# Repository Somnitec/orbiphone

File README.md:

Orbiphone (formerly WAMBAM or Toonpad)

A musical instrument making tones based on capacitive sensors.

todo:
Improve calibration algorhythmn
Make all buttons same color
Make button color related to tones pressed
Add subtle dynamic effects (bitcrushed reverb? multiply? things when buttons keep pressed?)

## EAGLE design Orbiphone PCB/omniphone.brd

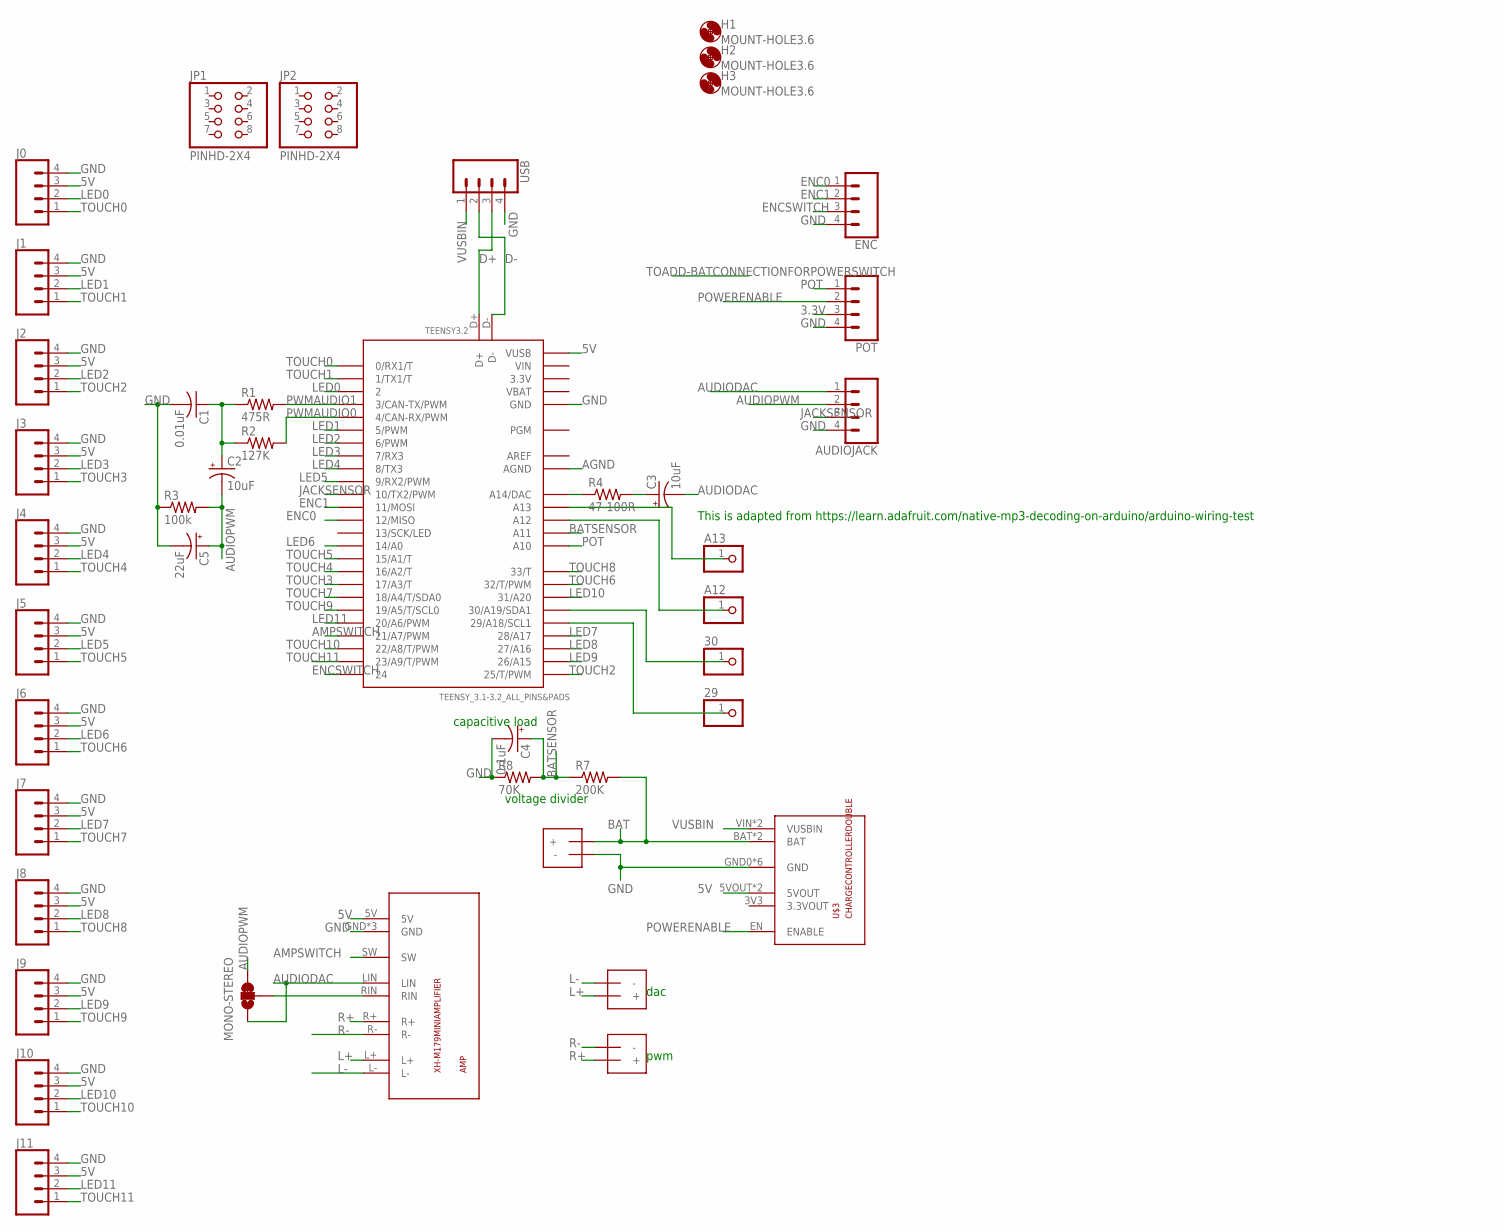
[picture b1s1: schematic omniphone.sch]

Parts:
29, 30: PINHD-1X1; 1X01
A12, A13: PINHD-1X1; 1X01
AMP: XH-M179MINIAMPLIFIER; XH-M179AMP
AUDIOJACK: CONN_04POLAR_LOCK; MOLEX-1X4_LOCK
BATTERY: SPEAKERTERMINAL-3.5MM; 1X2-3.5MM
C1: 0.01uF; C025-024X044
C2, C3: 10uF; E2-4
C4: 0.1uF; E2-4
C5: 22uF; E2-4
ENC: CONN_04POLAR_LOCK; MOLEX-1X4_LOCK
H1, H2, H3: MOUNT-HOLE3.6; 3,6
J0, J1, J2, J3, J4, J5, J6, J7, J8, J9, J10, J11: CONN_04POLAR_LOCK; MOLEX-1X4_LOCK
JP1, JP2: PINHD-2X4; 2X04
MONO-STEREO: JUMPER-SMT_3_1-NC_TRACE_SILK; SMT-JUMPER_3_1-NC_TRACE_SILK
POT: CONN_04POLAR_LOCK; MOLEX-1X4_LOCK
R1: 475R; 0204V
R2: 127K; 0204V
R3: 100k; 0204V
R4: 47-100R; 0204V
R7: 200K; 0204V
R8: 70K; 0204V
SPEAKERDAC: SPEAKERTERMINAL-3.5MM; 1X2-3.5MM
SPEAKERPWM: SPEAKERTERMINAL-3.5MM; 1X2-3.5MM
TEENSY3.2: TEENSY_3.1-3.2_ALL_PINS&PADS; TEENSY_3.0-3.2_ALL_PINS_&_PADS
U$3: CHARGECONTROLLERDOUBLE
USB: CONN_04POLAR_LOCK; MOLEX-1X4_LOCK

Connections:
3.3V: POT.3, TEENSY3.2.3.3V, TEENSY3.2.3.3V1 (3.3V), TEENSY3.2.3.3V2 (3.3V)
5V: AMP.5V, J0.3, J1.3, J2.3, J3.3, J4.3, J5.3, J6.3, J7.3, J8.3, J9.3, J10.3, J11.3, TEENSY3.2.VUSB, TEENSY3.2.VUSB1 (VUSB), U$3.5VOUT, U$3.5VOUT1 (5VOUT)
AGND: TEENSY3.2.AGND
AMPSWITCH: AMP.SW, TEENSY3.2.21/A7 (21/A7/PWM)
AREF: TEENSY3.2.AREF
AUDIODAC: AMP.LIN, AUDIOJACK.1, C3.-, MONO-STEREO.1
AUDIOPWM: AUDIOJACK.2, C2.-, C5.+, MONO-STEREO.3, R3.2
BAT: BATTERY.+, R7.2, U$3.BAT, U$3.BAT1 (BAT)
BATSENSOR: C4.+, R7.1, R8.2, TEENSY3.2.A11
D+: TEENSY3.2.D+, USB.3
D-: TEENSY3.2.D-, USB.2
ENC0: ENC.1, TEENSY3.2.12 (12/MISO)
ENC1: ENC.2, TEENSY3.2.11 (11/MOSI)
ENCSWITCH: ENC.3, TEENSY3.2.24
GND: AMP.GND, AMP.GND1 (GND), AMP.GND2 (GND), AUDIOJACK.4, BATTERY.-, C1.2, C4.-, C5.-, ENC.4, J0.4, J1.4, J2.4, J3.4, J4.4, J5.4, J6.4, J7.4, J8.4, J9.4, J10.4, J11.4, POT.4, R3.1, R8.1, TEENSY3.2.GND, TEENSY3.2.GND1 (GND), TEENSY3.2.GND2 (GND), TEENSY3.2.GND3 (GND), U$3.GND0 (GND), U$3.GND1 (GND), U$3.GND2 (GND), U$3.GND3 (GND), U$3.GND4 (GND), U$3.GND5 (GND), USB.4
JACKSENSOR: AUDIOJACK.3, TEENSY3.2.10 (10/TX2/PWM)
L+: AMP.L+, SPEAKERDAC.+
L-: AMP.L-, SPEAKERDAC.-
LED0: J0.2, TEENSY3.2.2
LED1: J1.2, TEENSY3.2.5 (5/PWM)
LED2: J2.2, TEENSY3.2.6 (6/PWM)
LED3: J3.2, TEENSY3.2.7 (7/RX3)
LED4: J4.2, TEENSY3.2.8 (8/TX3)
LED5: J5.2, TEENSY3.2.9 (9/RX2/PWM)
LED6: J6.2, TEENSY3.2.14/A0
LED7: J7.2, TEENSY3.2.28 (28/A17)
LED8: J8.2, TEENSY3.2.27 (27/A16)
LED9: J9.2, TEENSY3.2.26 (26/A15)
LED10: J10.2, TEENSY3.2.31 (31/A20)
LED11: J11.2, TEENSY3.2.20/A6 (20/A6/PWM)
unnamed: C1.1, C2.+, R1.1, R2.1
unnamed: A13.1, TEENSY3.2.A13
unnamed: A12.1, TEENSY3.2.A12
unnamed: R4.1, TEENSY3.2.RESET/DAC (A14/DAC)
unnamed: 30.1, TEENSY3.2.30 (30/A19/SDA1)
unnamed: C3.+, R4.2
unnamed: 29.1, TEENSY3.2.29 (29/A18/SCL1)
POT: POT.1, TEENSY3.2.A10
POWERENABLE: POT.2, U$3.EN (ENABLE)
PWMAUDIO0: R2.2, TEENSY3.2.4 (4/CAN-RX/PWM)
PWMAUDIO1: R1.2, TEENSY3.2.3 (3/CAN-TX/PWM)
R+: AMP.R+, SPEAKERPWM.+
R-: AMP.R-, SPEAKERPWM.-
RIN: AMP.RIN, MONO-STEREO.2
TOUCH0: J0.1, TEENSY3.2.0 (0/RX1/T)
TOUCH1: J1.1, TEENSY3.2.1 (1/TX1/T)
TOUCH2: J2.1, TEENSY3.2.25 (25/T/PWM)
TOUCH3: J3.1, TEENSY3.2.17/A3 (17/A3/T)
TOUCH4: J4.1, TEENSY3.2.16/A2 (16/A2/T)
TOUCH5: J5.1, TEENSY3.2.15/A1 (15/A1/T)
TOUCH6: J6.1, TEENSY3.2.32 (32/T/PWM)
TOUCH7: J7.1, TEENSY3.2.18/A4 (18/A4/T/SDA0)
TOUCH8: J8.1, TEENSY3.2.33 (33/T)
TOUCH9: J9.1, TEENSY3.2.19/A5 (19/A5/T/SCL0)
TOUCH10: J10.1, TEENSY3.2.22/A8 (22/A8/T/PWM)
TOUCH11: J11.1, TEENSY3.2.23/A9 (23/A9/T/PWM)
VBAT: TEENSY3.2.VBAT
VIN: TEENSY3.2.VIN
VUSBIN: U$3.VIN (VUSBIN), U$3.VIN1 (VUSBIN), USB.1

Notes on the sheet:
This is adapted from https://learn.adafruit.com/native-mp3-decoding-on-arduino/arduino-wiring-test
dac
pwm
voltage divider
capacitive load

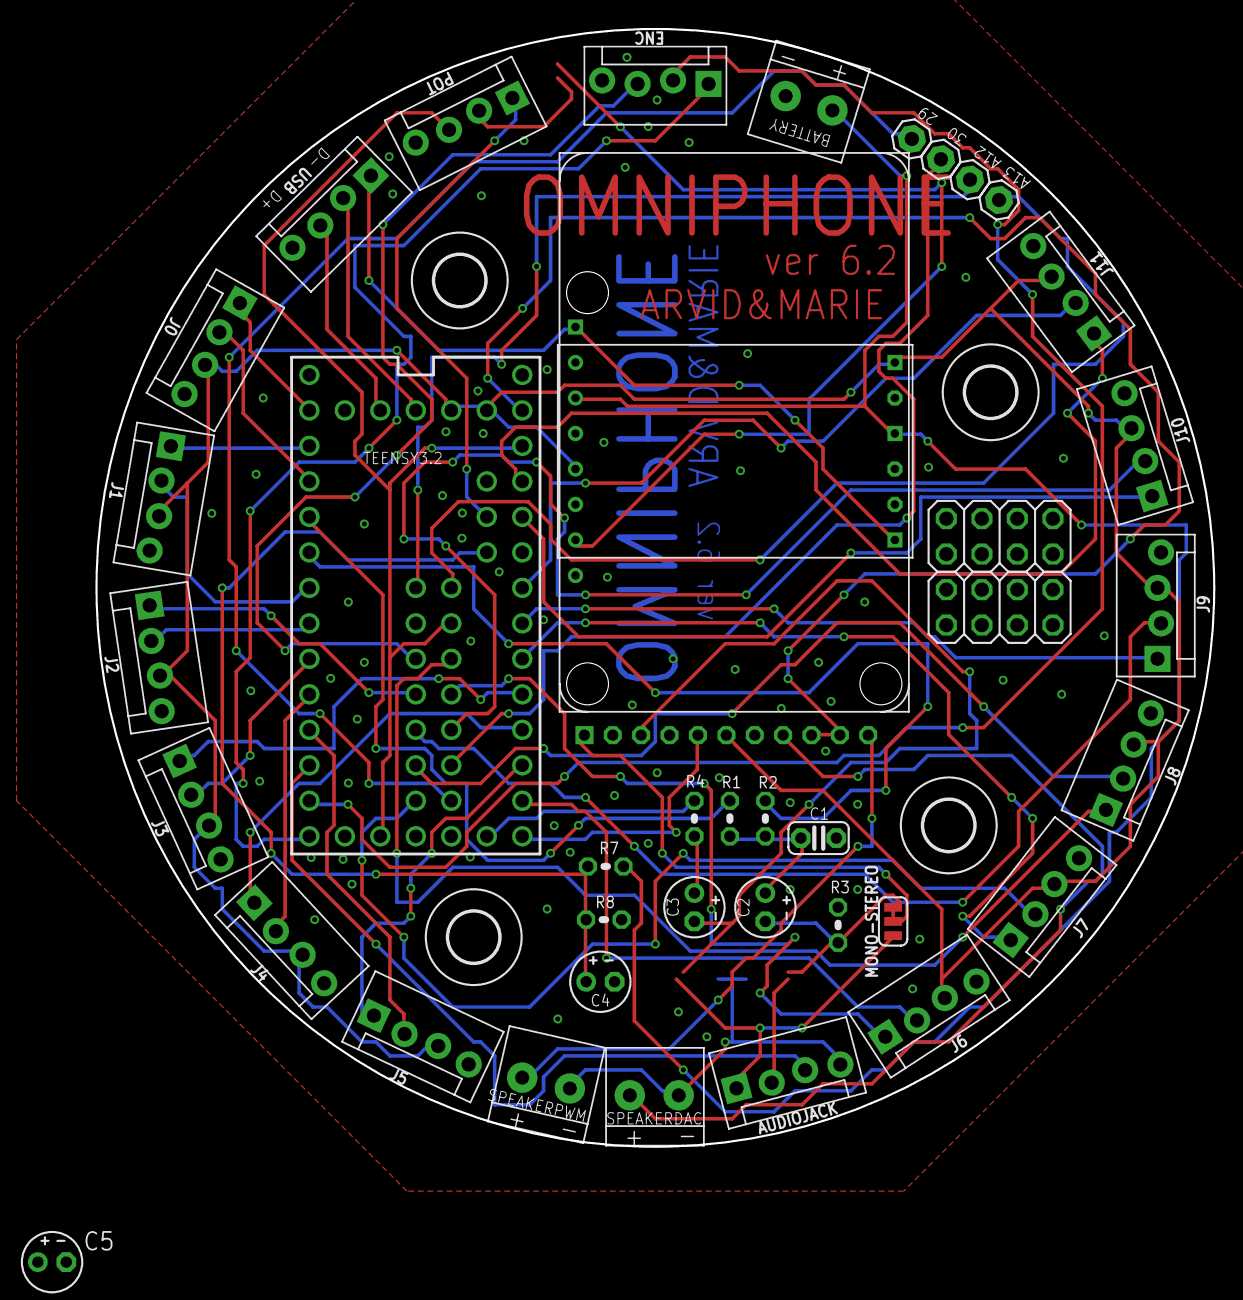
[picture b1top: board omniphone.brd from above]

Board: 2 copper layers, 80.0 x 80.0 mm, 44 parts (1 on the bottom side), 55 nets.

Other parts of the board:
H4: MOUNT-HOLE3.6; 3,6

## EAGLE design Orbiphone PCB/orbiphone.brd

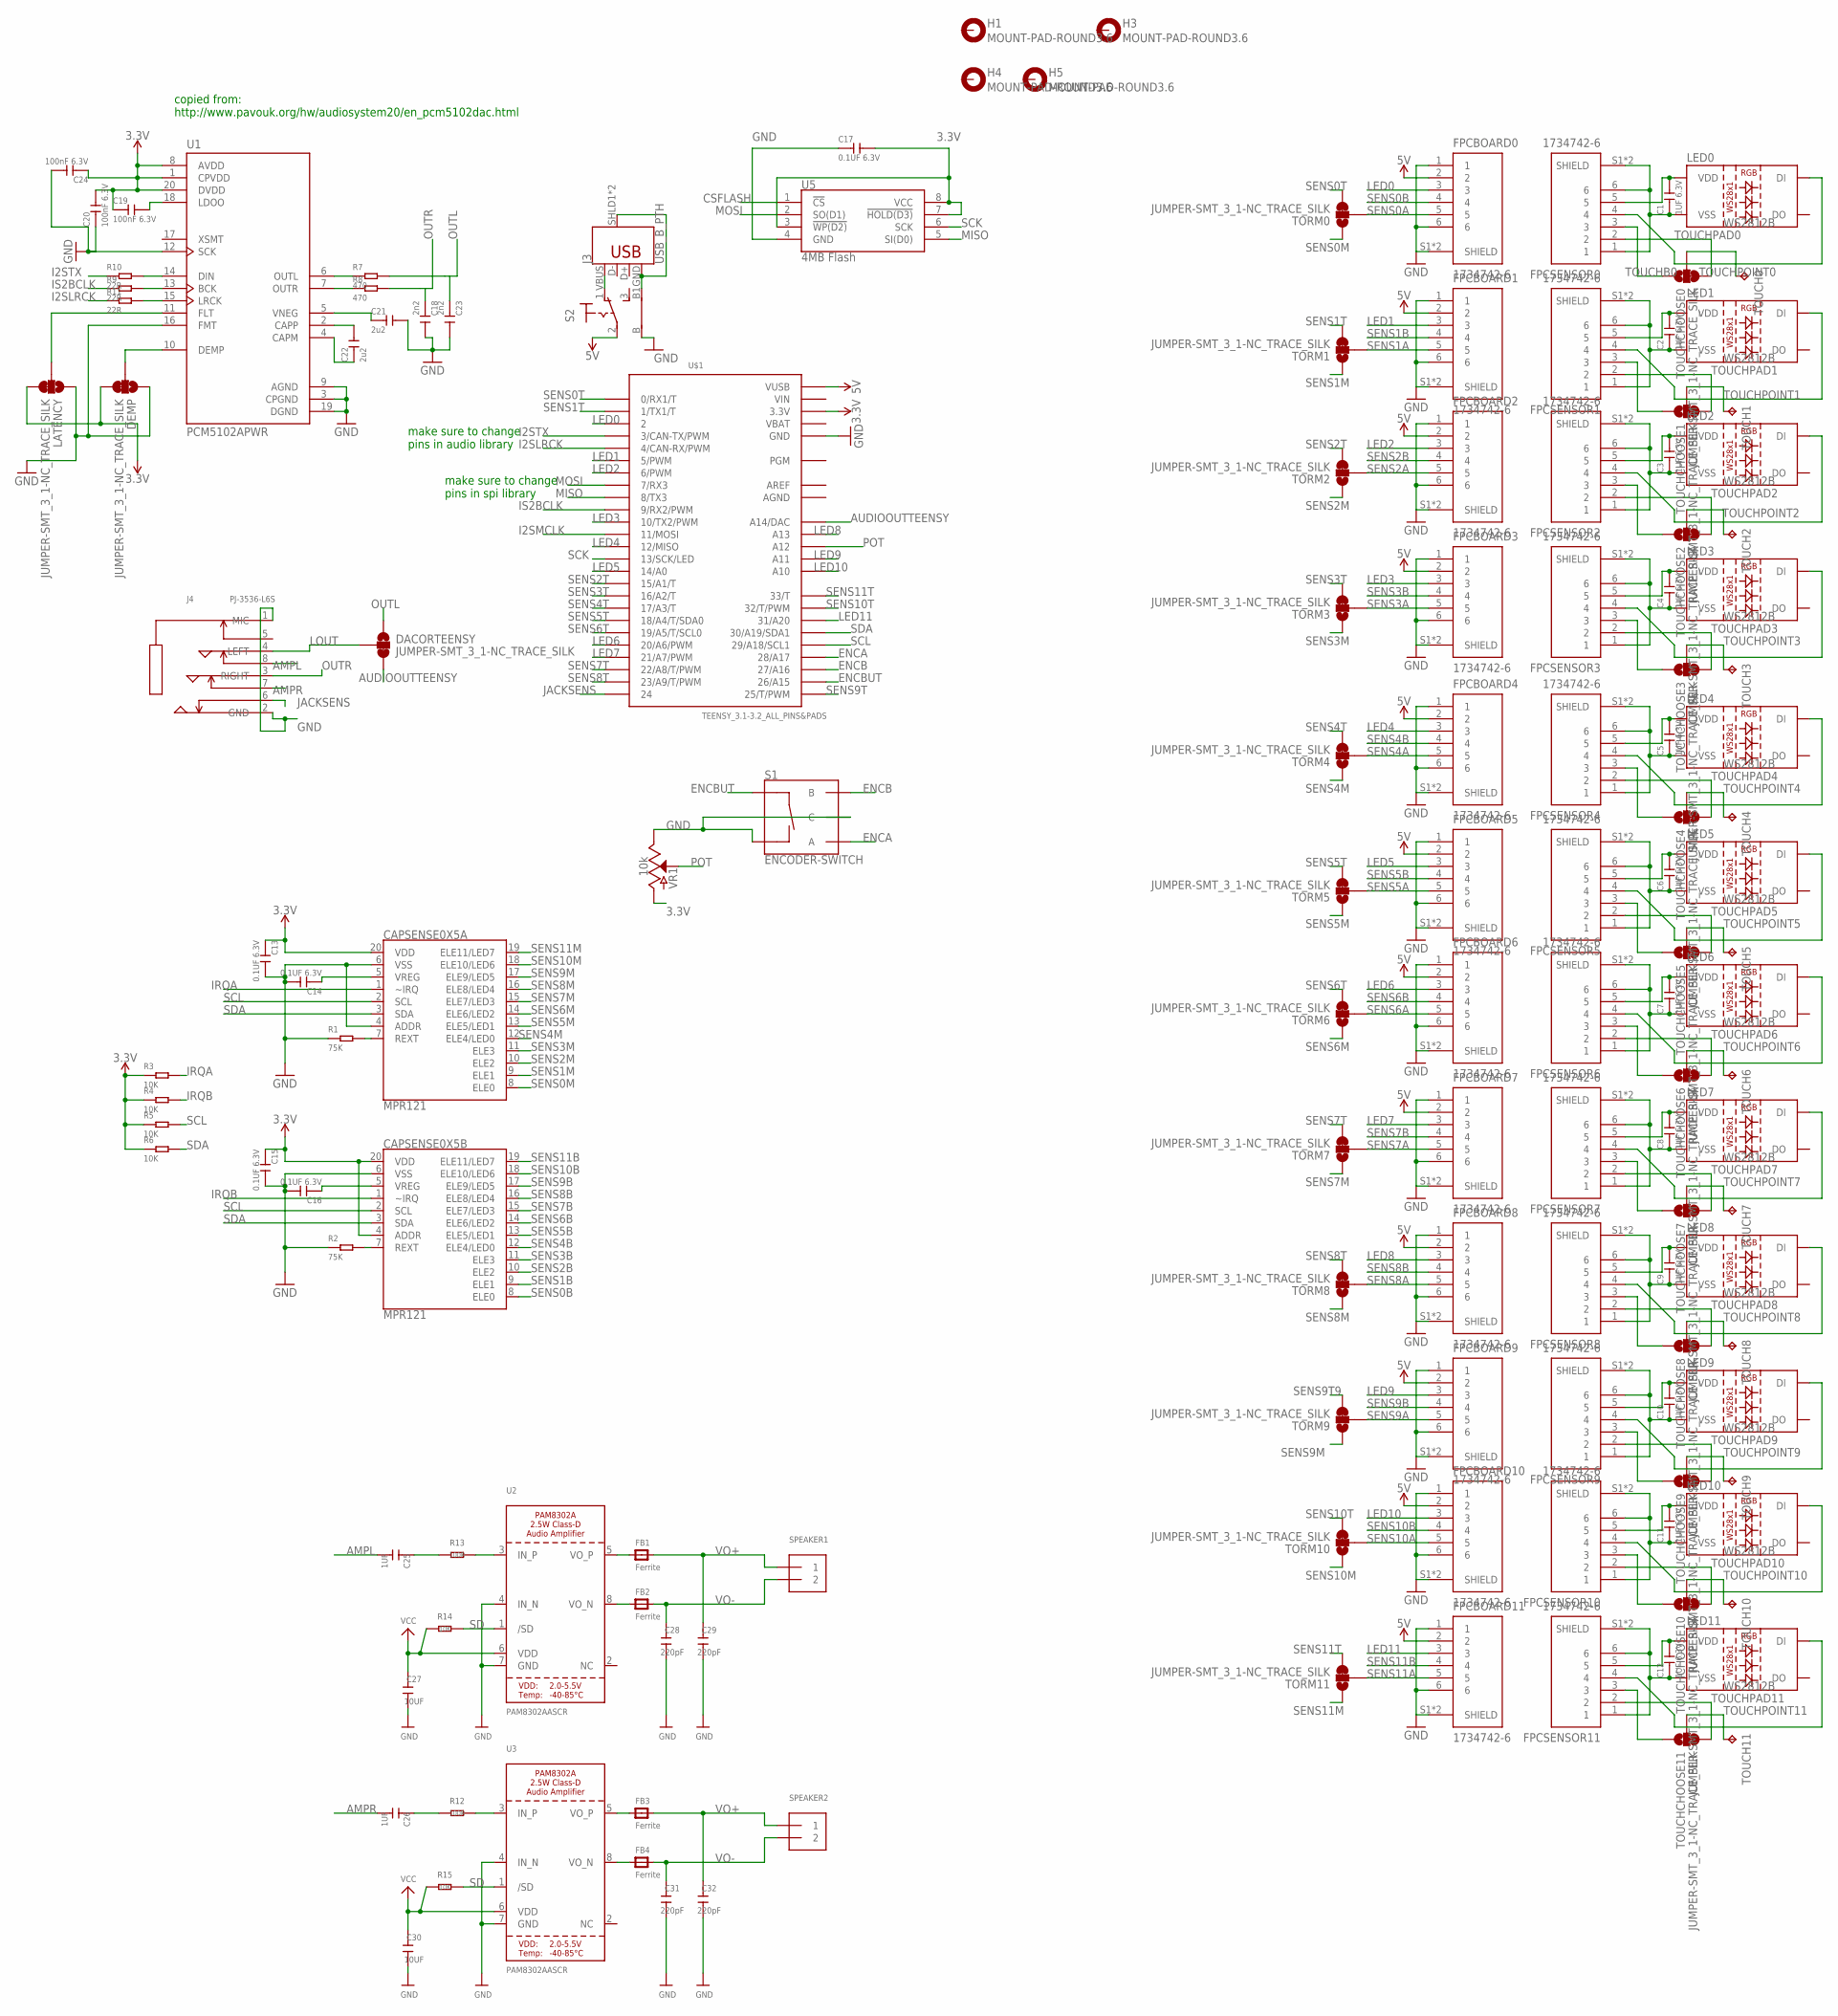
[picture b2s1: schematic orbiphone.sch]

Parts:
C1, C2, C3, C4, C5, C6, C7, C8, C9, C10, C11, C12: 1UF 6.3V; C0402
C13, C14, C15, C16, C17: 0.1UF 6.3V; C0402
C18, C23: 2n2; C0402
C19, C20, C24: 100nF 6.3V; C0402
C21, C22: 2u2; C0402
C25, C26: 1UF; C0402
C27, C30: 10UF; C0402
C28, C29, C31, C32: 220pF; C0402
CAPSENSE0X5A, CAPSENSE0X5B: MPR121; QFN-20
DACORTEENSY: JUMPER-SMT_3_1-NC_TRACE_SILK; SMT-JUMPER_3_1-NC_TRACE_SILK
DEMP: JUMPER-SMT_3_1-NC_TRACE_SILK; SMT-JUMPER_3_1-NC_TRACE_SILK
FB1, FB2, FB3, FB4: Ferrite; _0805
FPCBOARD0, FPCBOARD1, FPCBOARD2, FPCBOARD3, FPCBOARD4, FPCBOARD5, FPCBOARD6, FPCBOARD7, FPCBOARD8, FPCBOARD9, FPCBOARD10, FPCBOARD11: 1734742-6; TE_1734742-6
FPCSENSOR0, FPCSENSOR1, FPCSENSOR2, FPCSENSOR3, FPCSENSOR4, FPCSENSOR5, FPCSENSOR6, FPCSENSOR7, FPCSENSOR8, FPCSENSOR9, FPCSENSOR10, FPCSENSOR11: 1734742-6; TE_1734742-6
H1, H3, H4, H5: MOUNT-PAD-ROUND3.6; 3,6-PAD
J3: USB_B_PTH; USB-B-PTH
J4: PJ-3536-L6S; AUDIO8P-SMD-3.5-14.5X6X5MM
LATENCY: JUMPER-SMT_3_1-NC_TRACE_SILK; SMT-JUMPER_3_1-NC_TRACE_SILK
LED0, LED1, LED2, LED3, LED4, LED5, LED6, LED7, LED8, LED9, LED10, LED11: WS2812B
R1, R2: 75K; R0603
R3, R4, R5, R6: 10K; R0603
R7, R8: 470; R0603
R9, R10, R11: 22R; R0603
R12, R13: 100R; R0805
R14, R15: 10K; R0805
S1: ENCODER-SWITCH; ROTARY_ENC_PLAIN
S2: 316-917
SPEAKER1, SPEAKER2: TERMBLOCK_1X2; TERMBLOCK_1X2-3.5MM
TORM0, TORM1, TORM2, TORM3, TORM4, TORM5, TORM6, TORM7, TORM8, TORM9, TORM10, TORM11: JUMPER-SMT_3_1-NC_TRACE_SILK; SMT-JUMPER_3_1-NC_TRACE_SILK
TOUCH0, TOUCH1, TOUCH2, TOUCH3, TOUCH4, TOUCH5, TOUCH6, TOUCH7, TOUCH8, TOUCH9, TOUCH10, TOUCH11: TPPAD1-13; P1-13
TOUCHCHOOSE0, TOUCHCHOOSE1, TOUCHCHOOSE2, TOUCHCHOOSE3, TOUCHCHOOSE4, TOUCHCHOOSE5, TOUCHCHOOSE6, TOUCHCHOOSE7, TOUCHCHOOSE8, TOUCHCHOOSE9, TOUCHCHOOSE10, TOUCHCHOOSE11: JUMPER-SMT_3_1-NC_TRACE_SILK; SMT-JUMPER_3_1-NC_TRACE_SILK
U1: PCM5102APWR; SOP65P640X120-20N
U2, U3: PAM8302AASCR; MSOP8_0.65MM
U5: 4MB Flash; SO08
U$1: TEENSY_3.1-3.2_ALL_PINS&PADS; TEENSY_3.0-3.2_ALL_PINS_&_PADS
VR1: 10k; POT-PTH-ALPS-KIT

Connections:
3.3V: C13.1, C15.1, C17.2, C19.1, C20.2, C24.1, CAPSENSE0X5A.20 (VDD), CAPSENSE0X5B.4 (ADDR), CAPSENSE0X5B.20 (VDD), DEMP.3, LATENCY.3, R3.1, R4.1, R5.1, R6.1, U1.1 (CPVDD), U1.8 (AVDD), U1.20 (DVDD), U5.3 (!WP(D2)), U5.7 (!HOLD(D3)), U5.8 (VCC), U$1.3.3V, U$1.3.3V1 (3.3V), U$1.3.3V2 (3.3V), VR1.P$3 (A)
5V: FPCBOARD0.2, FPCBOARD1.2, FPCBOARD2.2, FPCBOARD3.2, FPCBOARD4.2, FPCBOARD5.2, FPCBOARD6.2, FPCBOARD7.2, FPCBOARD8.2, FPCBOARD9.2, FPCBOARD10.2, FPCBOARD11.2, S2.2, U$1.VUSB
AGND: U$1.AGND
AMPL: C25.2, J4.8
AMPR: C26.2, J4.7
AREF: U$1.AREF
AUDIOOUTTEENSY: DACORTEENSY.3, U$1.RESET/DAC (A14/DAC)
CSFLASH: U5.1 (!CS)
ENCA: S1.A, U$1.28 (28/A17)
ENCB: S1.B, U$1.27 (27/A16)
ENCBUT: S1.SW+, U$1.26 (26/A15)
GND: C13.2, C14.2, C15.2, C16.2, C17.1, C18.2, C20.1, C21.2, C23.2, C24.2, C27.2, C28.2, C29.2, C30.2, C31.2, C32.2, CAPSENSE0X5A.4 (ADDR), CAPSENSE0X5A.6 (VSS), CAPSENSE0X5B.6 (VSS), DEMP.1, FPCBOARD0.1, FPCBOARD0.6, FPCBOARD0.S1 (SHIELD), FPCBOARD0.S2 (SHIELD), FPCBOARD1.1, FPCBOARD1.6, FPCBOARD1.S1 (SHIELD), FPCBOARD1.S2 (SHIELD), FPCBOARD2.1, FPCBOARD2.6, FPCBOARD2.S1 (SHIELD), FPCBOARD2.S2 (SHIELD), FPCBOARD3.1, FPCBOARD3.6, FPCBOARD3.S1 (SHIELD), FPCBOARD3.S2 (SHIELD), FPCBOARD4.1, FPCBOARD4.6, FPCBOARD4.S1 (SHIELD), FPCBOARD4.S2 (SHIELD), FPCBOARD5.1, FPCBOARD5.6, FPCBOARD5.S1 (SHIELD), FPCBOARD5.S2 (SHIELD), FPCBOARD6.1, FPCBOARD6.6, FPCBOARD6.S1 (SHIELD), FPCBOARD6.S2 (SHIELD), FPCBOARD7.1, FPCBOARD7.6, FPCBOARD7.S1 (SHIELD), FPCBOARD7.S2 (SHIELD), FPCBOARD8.1, FPCBOARD8.6, FPCBOARD8.S1 (SHIELD), FPCBOARD8.S2 (SHIELD), FPCBOARD9.1, FPCBOARD9.6, FPCBOARD9.S1 (SHIELD), FPCBOARD9.S2 (SHIELD), FPCBOARD10.1, FPCBOARD10.6, FPCBOARD10.S1 (SHIELD), FPCBOARD10.S2 (SHIELD), FPCBOARD11.1, FPCBOARD11.6, FPCBOARD11.S1 (SHIELD), FPCBOARD11.S2 (SHIELD), J4.1 (MIC), J4.2 (GND), LATENCY.1, R1.1, R2.1, S1.C, S1.SW-, S2.B, U1.3 (CPGND), U1.9 (AGND), U1.12 (SCK), U1.16 (FMT), U1.19 (DGND), U2.4 (IN_N), U2.7 (GND), U3.4 (IN_N), U3.7 (GND), U5.4 (GND), U$1.GND, U$1.GND1 (GND), U$1.GND2 (GND), VR1.P$1 (E)
I2SLRCK: R11.1, U$1.4 (4/CAN-RX/PWM)
I2SMCLK: U$1.11 (11/MOSI)
I2STX: R10.1, U$1.3 (3/CAN-TX/PWM)
IRQA: CAPSENSE0X5A.1 (~IRQ), R3.2
IRQB: CAPSENSE0X5B.1 (~IRQ), R4.2
IS2BCLK: R9.1, U$1.9 (9/RX2/PWM)
JACKSENS: J4.6, U$1.24
LED0: FPCBOARD0.3, U$1.2
LED1: FPCBOARD1.3, U$1.5 (5/PWM)
LED2: FPCBOARD2.3, U$1.6 (6/PWM)
LED3: FPCBOARD3.3, U$1.10 (10/TX2/PWM)
LED4: FPCBOARD4.3, U$1.12 (12/MISO)
LED5: FPCBOARD5.3, U$1.14/A0
LED6: FPCBOARD6.3, U$1.20/A6 (20/A6/PWM)
LED7: FPCBOARD7.3, U$1.21/A7 (21/A7/PWM)
LED8: FPCBOARD8.3, U$1.A13
LED9: FPCBOARD9.3, U$1.A11
LED10: FPCBOARD10.3, U$1.A10
LED11: FPCBOARD11.3, U$1.31 (31/A20)
LOUT: DACORTEENSY.2, J4.4 (LEFT)
MISO: U5.5 (SI(D0)), U$1.8 (8/TX3)
MOSI: U5.2 (SO(D1)), U$1.7 (7/RX3)
unnamed: C1.1, FPCSENSOR0.1, FPCSENSOR0.6, FPCSENSOR0.S1 (SHIELD), FPCSENSOR0.S2 (SHIELD), LED0.3 (VSS)
unnamed: C2.1, FPCSENSOR1.1, FPCSENSOR1.6, FPCSENSOR1.S1 (SHIELD), FPCSENSOR1.S2 (SHIELD), LED1.3 (VSS)
unnamed: C1.2, FPCSENSOR0.5, LED0.1 (VDD)
unnamed: FPCSENSOR0.4, LED0.4 (DI)
unnamed: C2.2, FPCSENSOR1.5, LED1.1 (VDD)
unnamed: FPCSENSOR1.4, LED1.4 (DI)
unnamed: FPCSENSOR1.3, TOUCHCHOOSE1.1
unnamed: C3.1, FPCSENSOR2.1, FPCSENSOR2.6, FPCSENSOR2.S1 (SHIELD), FPCSENSOR2.S2 (SHIELD), LED2.3 (VSS)
unnamed: C3.2, FPCSENSOR2.5, LED2.1 (VDD)
unnamed: FPCSENSOR2.4, LED2.4 (DI)
unnamed: FPCSENSOR2.3, TOUCHCHOOSE2.1
unnamed: C4.1, FPCSENSOR3.1, FPCSENSOR3.6, FPCSENSOR3.S1 (SHIELD), FPCSENSOR3.S2 (SHIELD), LED3.3 (VSS)
unnamed: C4.2, FPCSENSOR3.5, LED3.1 (VDD)
unnamed: FPCSENSOR3.4, LED3.4 (DI)
unnamed: FPCSENSOR3.3, TOUCHCHOOSE3.1
unnamed: C5.1, FPCSENSOR4.1, FPCSENSOR4.6, FPCSENSOR4.S1 (SHIELD), FPCSENSOR4.S2 (SHIELD), LED4.3 (VSS)
unnamed: C5.2, FPCSENSOR4.5, LED4.1 (VDD)
unnamed: FPCSENSOR4.4, LED4.4 (DI)
unnamed: FPCSENSOR4.3, TOUCHCHOOSE4.1
unnamed: C6.1, FPCSENSOR5.1, FPCSENSOR5.6, FPCSENSOR5.S1 (SHIELD), FPCSENSOR5.S2 (SHIELD), LED5.3 (VSS)
unnamed: C6.2, FPCSENSOR5.5, LED5.1 (VDD)
unnamed: FPCSENSOR5.4, LED5.4 (DI)
unnamed: FPCSENSOR5.3, TOUCHCHOOSE5.1
unnamed: C7.1, FPCSENSOR6.1, FPCSENSOR6.6, FPCSENSOR6.S1 (SHIELD), FPCSENSOR6.S2 (SHIELD), LED6.3 (VSS)
unnamed: C7.2, FPCSENSOR6.5, LED6.1 (VDD)
unnamed: FPCSENSOR6.4, LED6.4 (DI)
unnamed: C14.1, CAPSENSE0X5A.5 (VREG)
unnamed: CAPSENSE0X5A.7 (REXT), R1.2
unnamed: J3.GND, J3.SHLD1 (SHIELD), J3.SHLD2 (SHIELD), S2.B1
unnamed: J3.VBUS, S2.1 (O)
unnamed: C16.1, CAPSENSE0X5B.5 (VREG)
unnamed: CAPSENSE0X5B.7 (REXT), R2.2
unnamed: R10.2, U1.14 (DIN)
unnamed: R9.2, U1.13 (BCK)
unnamed: R11.2, U1.15 (LRCK)
unnamed: C19.2, U1.18 (LDOO)
unnamed: C22.2, U1.2 (CAPP)
unnamed: C22.1, U1.4 (CAPM)
unnamed: C21.1, U1.5 (VNEG)
unnamed: R7.1, U1.6 (OUTL)
unnamed: R8.1, U1.7 (OUTR)
unnamed: LATENCY.2, U1.11 (FLT)
unnamed: DEMP.2, U1.10 (DEMP)
unnamed: R12.2, U3.3 (IN_P)
unnamed: R13.2, U2.3 (IN_P)
unnamed: FB4.1, U3.8 (VO_N)
unnamed: FB2.1, U2.8 (VO_N)
unnamed: FB1.1, U2.5 (VO_P)
unnamed: C25.1, R13.1
unnamed: FB3.1, U3.5 (VO_P)
unnamed: C26.1, R12.1
unnamed: FPCSENSOR6.3, TOUCHCHOOSE6.1
unnamed: C8.1, FPCSENSOR7.1, FPCSENSOR7.6, FPCSENSOR7.S1 (SHIELD), FPCSENSOR7.S2 (SHIELD), LED7.3 (VSS)
unnamed: C8.2, FPCSENSOR7.5, LED7.1 (VDD)
unnamed: FPCSENSOR7.4, LED7.4 (DI)
unnamed: FPCSENSOR7.3, TOUCHCHOOSE7.1
unnamed: C9.1, FPCSENSOR8.1, FPCSENSOR8.6, FPCSENSOR8.S1 (SHIELD), FPCSENSOR8.S2 (SHIELD), LED8.3 (VSS)
unnamed: C9.2, FPCSENSOR8.5, LED8.1 (VDD)
unnamed: FPCSENSOR8.4, LED8.4 (DI)
unnamed: FPCSENSOR8.3, TOUCHCHOOSE8.1
unnamed: C10.1, FPCSENSOR9.1, FPCSENSOR9.6, FPCSENSOR9.S1 (SHIELD), FPCSENSOR9.S2 (SHIELD), LED9.3 (VSS)
unnamed: C10.2, FPCSENSOR9.5, LED9.1 (VDD)
unnamed: FPCSENSOR9.4, LED9.4 (DI)
unnamed: FPCSENSOR9.3, TOUCHCHOOSE9.1
unnamed: C11.1, FPCSENSOR10.1, FPCSENSOR10.6, FPCSENSOR10.S1 (SHIELD), FPCSENSOR10.S2 (SHIELD), LED10.3 (VSS)
unnamed: C11.2, FPCSENSOR10.5, LED10.1 (VDD)
unnamed: FPCSENSOR10.4, LED10.4 (DI)
unnamed: FPCSENSOR10.3, TOUCHCHOOSE10.1
unnamed: C12.1, FPCSENSOR11.1, FPCSENSOR11.6, FPCSENSOR11.S1 (SHIELD), FPCSENSOR11.S2 (SHIELD), LED11.3 (VSS)
unnamed: C12.2, FPCSENSOR11.5, LED11.1 (VDD)
unnamed: FPCSENSOR11.4, LED11.4 (DI)
unnamed: FPCSENSOR11.3, TOUCHCHOOSE11.1
OUTL: C23.1, DACORTEENSY.1, R7.2
OUTR: C18.1, J4.3 (RIGHT), R8.2
POT: U$1.A12, VR1.P$2 (S)
SCK: U5.6 (SCK), U$1.13 (13/SCK/LED)
SCL: CAPSENSE0X5A.2 (SCL), CAPSENSE0X5B.2 (SCL), R5.2, U$1.29 (29/A18/SCL1)
SD: R14.2, R15.2, U2.1 (/SD), U3.1 (/SD)
SDA: CAPSENSE0X5A.3 (SDA), CAPSENSE0X5B.3 (SDA), R6.2, U$1.30 (30/A19/SDA1)
SENS0A: FPCBOARD0.5, TORM0.2
SENS0B: CAPSENSE0X5B.8 (ELE0), FPCBOARD0.4
SENS0M: CAPSENSE0X5A.8 (ELE0), TORM0.1
SENS0T: TORM0.3, U$1.0 (0/RX1/T)
SENS1A: FPCBOARD1.5, TORM1.2
SENS1B: CAPSENSE0X5B.9 (ELE1), FPCBOARD1.4
SENS1M: CAPSENSE0X5A.9 (ELE1), TORM1.1
SENS1T: TORM1.3, U$1.1 (1/TX1/T)
SENS2A: FPCBOARD2.5, TORM2.2
SENS2B: CAPSENSE0X5B.10 (ELE2), FPCBOARD2.4
SENS2M: CAPSENSE0X5A.10 (ELE2), TORM2.1
SENS2T: TORM2.3, U$1.15/A1 (15/A1/T)
SENS3A: FPCBOARD3.5, TORM3.2
SENS3B: CAPSENSE0X5B.11 (ELE3), FPCBOARD3.4
SENS3M: CAPSENSE0X5A.11 (ELE3), TORM3.1
SENS3T: TORM3.3, U$1.16/A2 (16/A2/T)
SENS4A: FPCBOARD4.5, TORM4.2
SENS4B: CAPSENSE0X5B.12 (ELE4/LED0), FPCBOARD4.4
SENS4M: CAPSENSE0X5A.12 (ELE4/LED0), TORM4.1
SENS4T: TORM4.3, U$1.17/A3 (17/A3/T)
SENS5A: FPCBOARD5.5, TORM5.2
SENS5B: CAPSENSE0X5B.13 (ELE5/LED1), FPCBOARD5.4
SENS5M: CAPSENSE0X5A.13 (ELE5/LED1), TORM5.1
SENS5T: TORM5.3, U$1.18/A4 (18/A4/T/SDA0)
SENS6A: FPCBOARD6.5, TORM6.2
SENS6B: CAPSENSE0X5B.14 (ELE6/LED2), FPCBOARD6.4
SENS6M: CAPSENSE0X5A.14 (ELE6/LED2), TORM6.1
SENS6T: TORM6.3, U$1.19/A5 (19/A5/T/SCL0)
SENS7A: FPCBOARD7.5, TORM7.2
SENS7B: CAPSENSE0X5B.15 (ELE7/LED3), FPCBOARD7.4
SENS7M: CAPSENSE0X5A.15 (ELE7/LED3), TORM7.1
SENS7T: TORM7.3, U$1.22/A8 (22/A8/T/PWM)
SENS8A: FPCBOARD8.5, TORM8.2
SENS8B: CAPSENSE0X5B.16 (ELE8/LED4), FPCBOARD8.4
SENS8M: CAPSENSE0X5A.16 (ELE8/LED4), TORM8.1
SENS8T: TORM8.3, U$1.23/A9 (23/A9/T/PWM)
SENS9A: FPCBOARD9.5, TORM9.2
SENS9B: CAPSENSE0X5B.17 (ELE9/LED5), FPCBOARD9.4
SENS9M: CAPSENSE0X5A.17 (ELE9/LED5), TORM9.1
SENS9T: U$1.25 (25/T/PWM)
SENS9T9: TORM9.3
SENS10A: FPCBOARD10.5, TORM10.2
SENS10B: CAPSENSE0X5B.18 (ELE10/LED6), FPCBOARD10.4
SENS10M: CAPSENSE0X5A.18 (ELE10/LED6), TORM10.1
SENS10T: TORM10.3, U$1.32 (32/T/PWM)
SENS11A: FPCBOARD11.5, TORM11.2
SENS11B: CAPSENSE0X5B.19 (ELE11/LED7), FPCBOARD11.4
SENS11M: CAPSENSE0X5A.19 (ELE11/LED7), TORM11.1
SENS11T: TORM11.3, U$1.33 (33/T)
TOUCHB0: FPCSENSOR0.3, TOUCHCHOOSE0.1
TOUCHPAD0: FPCSENSOR0.2, TOUCHCHOOSE0.3
TOUCHPAD1: FPCSENSOR1.2, TOUCHCHOOSE1.3
TOUCHPAD2: FPCSENSOR2.2, TOUCHCHOOSE2.3
TOUCHPAD3: FPCSENSOR3.2, TOUCHCHOOSE3.3
TOUCHPAD4: FPCSENSOR4.2, TOUCHCHOOSE4.3
TOUCHPAD5: FPCSENSOR5.2, TOUCHCHOOSE5.3
TOUCHPAD6: FPCSENSOR6.2, TOUCHCHOOSE6.3
TOUCHPAD7: FPCSENSOR7.2, TOUCHCHOOSE7.3
TOUCHPAD8: FPCSENSOR8.2, TOUCHCHOOSE8.3
TOUCHPAD9: FPCSENSOR9.2, TOUCHCHOOSE9.3
TOUCHPAD10: FPCSENSOR10.2, TOUCHCHOOSE10.3
TOUCHPAD11: FPCSENSOR11.2, TOUCHCHOOSE11.3
TOUCHPOINT0: TOUCH0.TP, TOUCHCHOOSE0.2
TOUCHPOINT1: TOUCH1.TP, TOUCHCHOOSE1.2
TOUCHPOINT2: TOUCH2.TP, TOUCHCHOOSE2.2
TOUCHPOINT3: TOUCH3.TP, TOUCHCHOOSE3.2
TOUCHPOINT4: TOUCH4.TP, TOUCHCHOOSE4.2
TOUCHPOINT5: TOUCH5.TP, TOUCHCHOOSE5.2
TOUCHPOINT6: TOUCH6.TP, TOUCHCHOOSE6.2
TOUCHPOINT7: TOUCH7.TP, TOUCHCHOOSE7.2
TOUCHPOINT8: TOUCH8.TP, TOUCHCHOOSE8.2
TOUCHPOINT9: TOUCH9.TP, TOUCHCHOOSE9.2
TOUCHPOINT10: TOUCH10.TP, TOUCHCHOOSE10.2
TOUCHPOINT11: TOUCH11.TP, TOUCHCHOOSE11.2
VBAT: U$1.VBAT
VCC: C27.1, C30.1, R14.1, R15.1, U2.6 (VDD), U3.6 (VDD)
VIN: U$1.VIN
VO+: C29.1, C32.1, FB1.2, FB3.2, SPEAKER1.1, SPEAKER2.1
VO-: C28.1, C31.1, FB2.2, FB4.2, SPEAKER1.2, SPEAKER2.2

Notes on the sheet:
make sure to change pins in spi library
make sure to change pins in audio library
copied from: http://www.pavouk.org/hw/audiosystem20/en_pcm5102dac.html

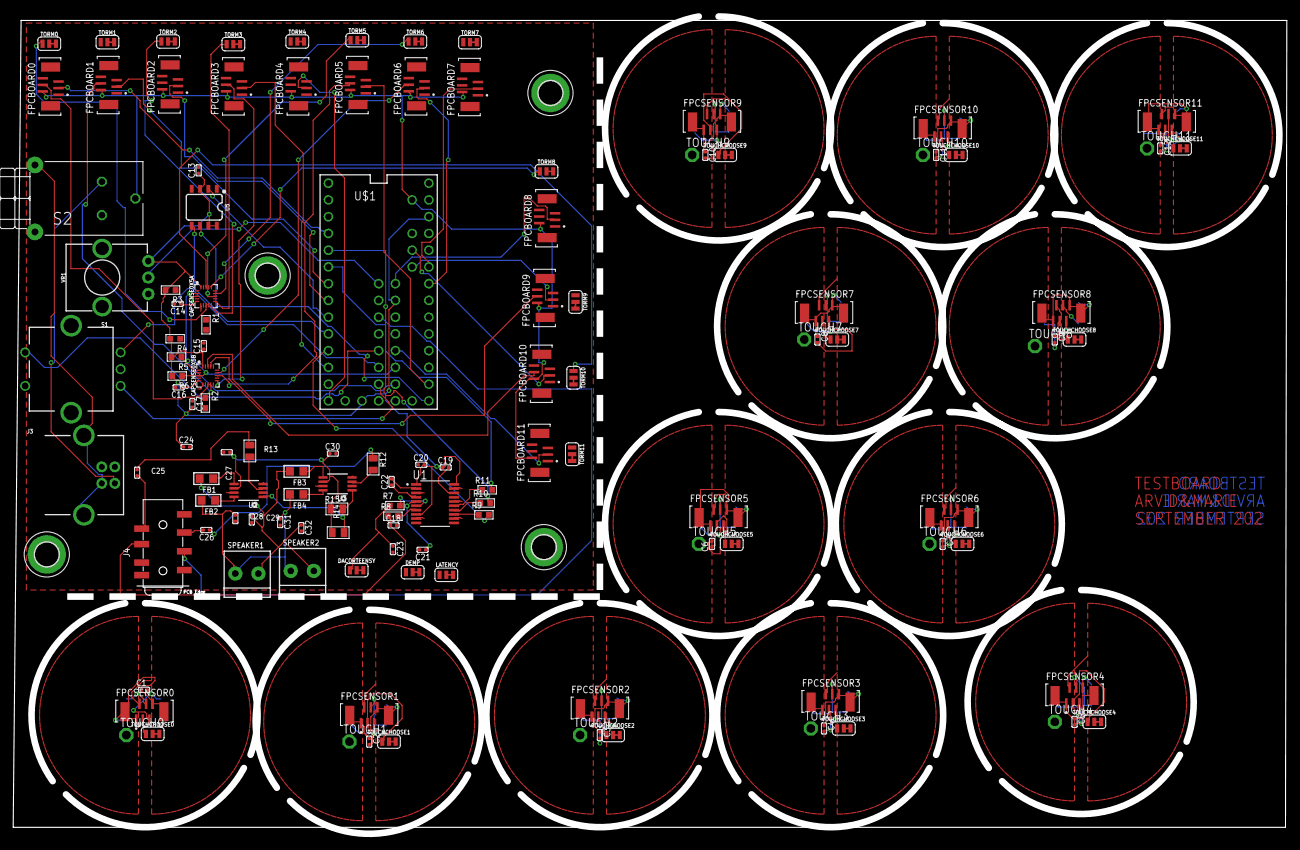
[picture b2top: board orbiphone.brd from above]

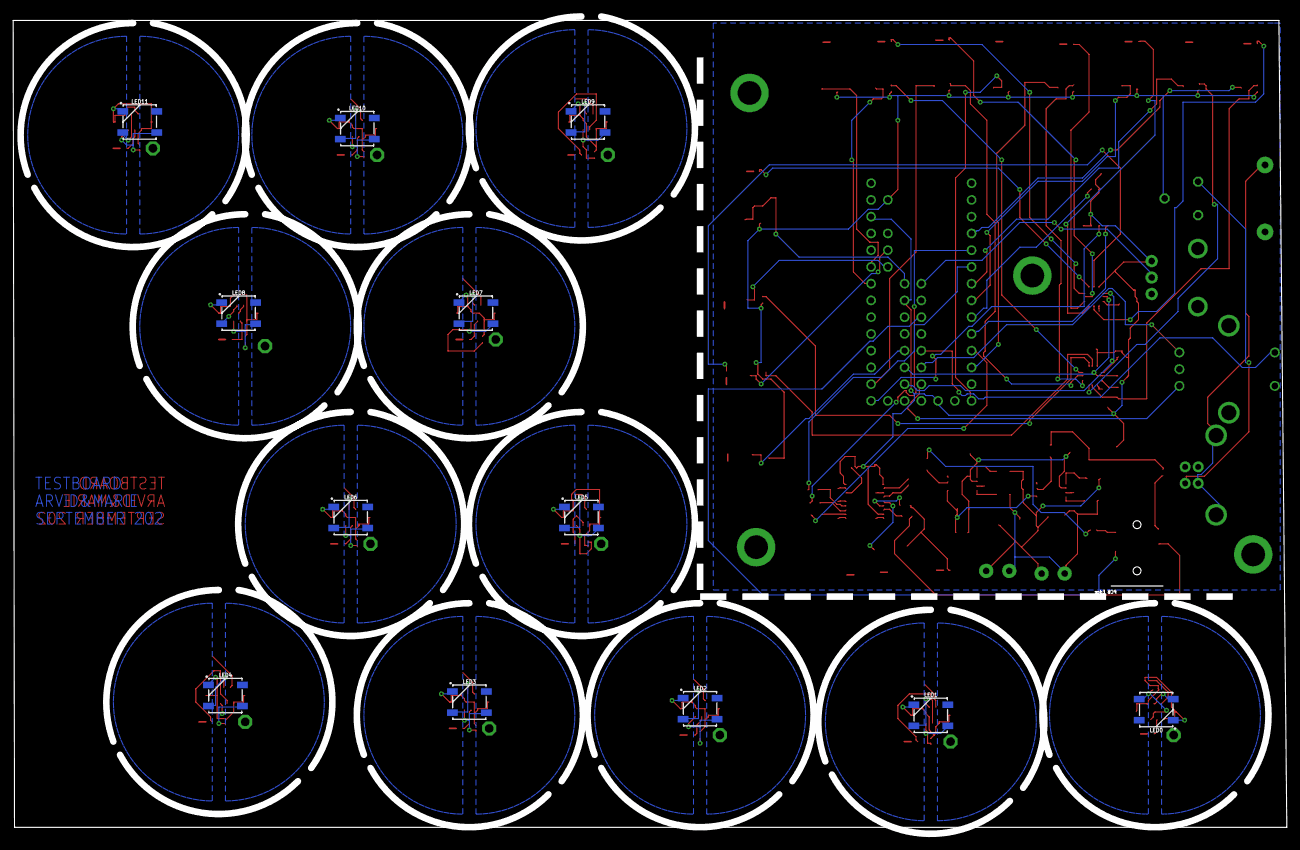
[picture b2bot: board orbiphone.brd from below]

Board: 2 copper layers, 193.2 x 124.0 mm, 144 parts (12 on the bottom side), 184 nets.

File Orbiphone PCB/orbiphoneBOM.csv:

Qty,Value,Device,Package,Parts,Description,ARROW_ASIA-PURCHASE-URL,AVAILABILITY,COMMENT,DESCRIPTION,DIGIKEY-PURCHASE-URL,EU_ROHS_COMPLIANCE,MF,MOUSER-PURCHASE-URL,MP,MPN,PACKAGE,POPULARITY,PRICE,PROD_ID,SF_ID,SF_SKU,TEXAS_INSTRUMENTS-PURCHASE-URL,TP_SIGNAL_NAME
1,,316-917,316-917,S2,TOGGLE SWITCH,,,,,,,,,,,,0,,,,,,
2,,TERMBLOCK_1X2,TERMBLOCK_1X2-3.5MM,"SPEAKER1, SPEAKER2",3.5mm Terminal block,,,,,,,,,,,,,,,,,,
5,0.1UF 6.3V,CERAMIC-1UF-6.3V-10%-X5R(0402),C0402,"C13, C14, C15, C16, C17",302010003,,,,,,,,,,CC0402KRX5R5BB105,,,,,,,,
2,100R,SMD-RES-100R-1%-1/8W(0805),R0805,"R12, R13",301012151,,,,,,,,,,RC0805JR-071KL,,,,,,,,
3,100nF 6.3V,CERAMIC-1UF-6.3V-10%-X5R(0402),C0402,"C19, C20, C24",302010003,,,,,,,,,,CC0402KRX5R5BB105,,,,,,,,
2,10K,SMD-RES-100R-1%-1/8W(0805),R0805,"R14, R15",301012151,,,,,,,,,,RC0805JR-071KL,,,,,,,,
4,10K,SMD-RES-75K-1%-1/10W(0603),R0603,"R3, R4, R5, R6",301012096,,,,,,,,,,RC0603FR-071K5L,,,,,,,,
2,10UF,CERAMIC-1UF-6.3V-10%-X5R(0402),C0402,"C27, C30",302010003,,,,,,,,,,CC0402KRX5R5BB105,,,,,,,,
1,10k,POTENTIOMETER-PTH-9MM-1/20W-20%-KIT,POT-PTH-ALPS-KIT,VR1,Potentiometer (Pot),,,,,,,,,,,,,,RES-09177,,COM-09288,,
24,1734742-6,1734742-6,TE_1734742-6,"FPCBOARD0, FPCBOARD1, FPCBOARD2, FPCBOARD3, FPCBOARD4, FPCBOARD5, FPCBOARD6, FPCBOARD7, FPCBOARD8, FPCBOARD9, FPCBOARD10, FPCBOARD11, FPCSENSOR0, FPCSENSOR1, FPCSENSOR2, FPCSENSOR3, FPCSENSOR4, FPCSENSOR5, FPCSENSOR6, FPCSENSOR7, FPCSENSOR8, FPCSENSOR9, FPCSENSOR10, FPCSENSOR11",Check prices,,Warning,1734742-6, Conn FPC Connector SKT 6 POS 0.5mm Solder ST SMD T/R ,https://snapeda.com/shop?store=DigiKey&id=501394,Compliant,TE Connectivity,https://snapeda.com/shop?store=Mouser&id=501394,1734742-6,,None,,None,,,,,
2,1UF,CERAMIC-1UF-6.3V-10%-X5R(0402),C0402,"C25, C26",302010003,,,,,,,,,,CC0402KRX5R5BB105,,,,,,,,
12,1UF 6.3V,CERAMIC-1UF-6.3V-10%-X5R(0402),C0402,"C1, C2, C3, C4, C5, C6, C7, C8, C9, C10, C11, C12",302010003,,,,,,,,,,CC0402KRX5R5BB105,,,,,,,,
4,220pF,CERAMIC-1UF-6.3V-10%-X5R(0402),C0402,"C28, C29, C31, C32",302010003,,,,,,,,,,CC0402KRX5R5BB105,,,,,,,,
3,22R,SMD-RES-75K-1%-1/10W(0603),R0603,"R9, R10, R11",301012096,,,,,,,,,,RC0603FR-071K5L,,,,,,,,
2,2n2,CERAMIC-1UF-6.3V-10%-X5R(0402),C0402,"C18, C23",302010003,,,,,,,,,,CC0402KRX5R5BB105,,,,,,,,
2,2u2,CERAMIC-1UF-6.3V-10%-X5R(0402),C0402,"C21, C22",302010003,,,,,,,,,,CC0402KRX5R5BB105,,,,,,,,
2,470,SMD-RES-75K-1%-1/10W(0603),R0603,"R7, R8",301012096,,,,,,,,,,RC0603FR-071K5L,,,,,,,,
1,4MB Flash,AT25SF041,SO08,U5,AT25SF041 4Mb Serial Flash Memory,,,,,,,,,,,,,,IC-12455,,,,
2,75K,SMD-RES-75K-1%-1/10W(0603),R0603,"R1, R2",301012096,,,,,,,,,,RC0603FR-071K5L,,,,,,,,
1,ENCODER-SWITCH,ENCODER-SWITCH,ROTARY_ENC_PLAIN,S1,Rotary Encoder w/ Select Switch,,,,,,,,,,,,,,,,COM-09117,,
4,Ferrite,FERRITE_0805,_0805,"FB1, FB2, FB3, FB4",Ferrite Bead,,,,,,,,,,,,,,,,,,
2,MPR121,MPR121,QFN-20,"CAPSENSE0X5A, CAPSENSE0X5B",NXP MPR121 Proximity Capacitive Touch Sensor Controller,,,,,,,,,,,,,,IC-09490,COM-09604,,,
2,PAM8302AASCR,AUDIOAMP_PAM8302A,MSOP8_0.65MM,"U2, U3",PAM8302A - 2.5W Class-D Mono Audio Amplifier,,,,,,,,,,,,,,,,,,
1,PCM5102APWR,PCM5102APWR,SOP65P640X120-20N,U1,"2VRMS DirectPath, 112dB Audio Stereo DAC with 32-bit, 384kHz PCM Interface 20-TSSOP -25 to 85  Check prices",https://snapeda.com/shop?store=Arrow+Asia&id=380885,Warning,, 2VRMS DirectPath&trade,", 112dB Audio Stereo DAC with 32-bit, 384kHz PCM Interface 20-TSSOP -25 to 85 ",,,Texas Instruments,https://snapeda.com/shop?store=Mouser&id=380885,PCM5102APWR,,TSSOP-20 Texas Instruments,,None,,,,https://snapeda.com/shop?store=Texas+Instruments&id=380885
1,PJ-3536-L6S,AUDIO-JACK-SMD-8P(PJ-3536-L6S),AUDIO8P-SMD-3.5-14.5X6X5MM,J4,Seeed SKU 320040003 - SMD Audio Jack 3.5mm 4 Degree,,,,,,,,,,PJ-3536-L6S,,,,,,,,
1,USB_B_PTH,USB_B_PTH,USB-B-PTH,J3,USB Type B Connector,,,,,,,,,,,,,,CONN-08278,PRT-00139,,,
12,,"FFC / FPC Cable, 6 Core, 0.5 mm, Same Sided Contacts, 6 "", 150-200mm",,,to be ordered but not assembled. example source: https://nl.farnell.com/multicomp-pro/mp-ffca05061522a/ffc-co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,,,,,,,,,,,,,,,,,,

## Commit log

2017-05-10 base code
    the code as I wrote it before making the github
2017-05-11 Turned momentaries into switched
2017-05-11 For some reason this didn't get commited
2017-05-11 added gitignore
2017-05-11 Removed LED color differenct
2017-07-05 fix of 6 tone
2020-07-22 MPE implemented for a single tone set
2020-07-22 Fix for allowing all buttons to be pressed
2020-07-22 added midi cc for the button presses
2020-07-24 Basic code with leds and MPR121
2020-08-25 something for the test setup
2020-08-25 name change (removed muziekgebouw aan t IJ)
2020-08-25 Added a potential pin mapping
2020-08-25 added audio test
2020-08-26 basic functions test
2020-08-27 old code adapted to work on new one!
2020-08-27 made it clear that leds can be updated individually in the testfile
2020-08-27 functional pentatonic orbiphone!
2020-08-27 made sound louder and fixed labels on setial plotter
2020-08-27 changed calibration values in touch.c and adjusted the other code to match
2020-08-28 tweaked the calibration a bit, will need to be rewritten for more sensitivity
2020-09-01 added volume button
2020-09-01 unsucessfully worked on calibration algo and added tone and timbre mod
2020-09-21 last modifications
2020-09-22 updated test file for new pin mapping
2020-09-22 all functional, although pwm+dac makes weird AM noises
2020-09-26 Added eagle files
2020-09-26 added speaker and headphone fixes
2020-09-26 changed the ampswitch as 13 doesn't work with its led on it
2020-09-26 preparations for powerswitch modification
2020-09-26 added a second set of oscillator, but didn't activate them yet
2020-09-26 added sub oscilator for vibration speaker
2020-09-26 added speaker off mode (by holding the button while starting up)
2020-09-26 added whole tone scale
2020-09-26 fixed the stepping direction through the tone tables
2020-09-26 added filter, still need to control them by speed of change
2020-09-27 basic example made for implementing slow and fast change rate
2020-09-27 remade an automatic calibration
2020-09-27 close but can be simplified
2020-09-27 fixed the bug, will start without bugging now
2020-09-27 new autocalib
2020-09-27 auto calibration ready for implementation in main file
2020-09-27 implemented metro library, but some clear faults
2020-09-27 made a start for a complete rewrite
2020-09-27 leds and graph working beautifully
2020-09-27 changerate mapped to led color
2020-09-27 sound but some pads are constantly lit
2020-09-27 pad 4 potentially fixed + encoder implemented
2020-09-27 fixed timbre switch and removed glide as it had a potential detuning bug
2020-09-27 attempting to remove clicking, but realizing I need an envelope for that
2020-09-27 proper envelopes implemented
2020-09-27 pretty decent opening filter from standard dev
2020-09-27 added more scales and no-speaker-mode
2020-09-28 opened up old files, this one not produced
2020-09-29 reduced to four tone sets
2020-09-29 a small sensitivity adjustment
2020-09-29 removed initializing sketch and added a nice startup fade
2020-09-29 small calibration tweak LEFT THIS VERSION AT REINAERDE
2021-11-16 not sure what;s changed
2021-12-10 flipped speaker on off mode on startup for muziekgebouw aan t ij

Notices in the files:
parts and their libraries:
SparkFun-Connectors: Licensing: Creative Commons ShareAlike 4.0 International - https://creativecommons.org/licenses/by-sa/4.0
microbuilder: This work is placed in the public domain, and may be freely used for commercial and non-commercial work with the following conditions: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
